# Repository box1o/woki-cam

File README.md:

# woki cam

modular infrared camera for optical tracking of retroreflective markers.

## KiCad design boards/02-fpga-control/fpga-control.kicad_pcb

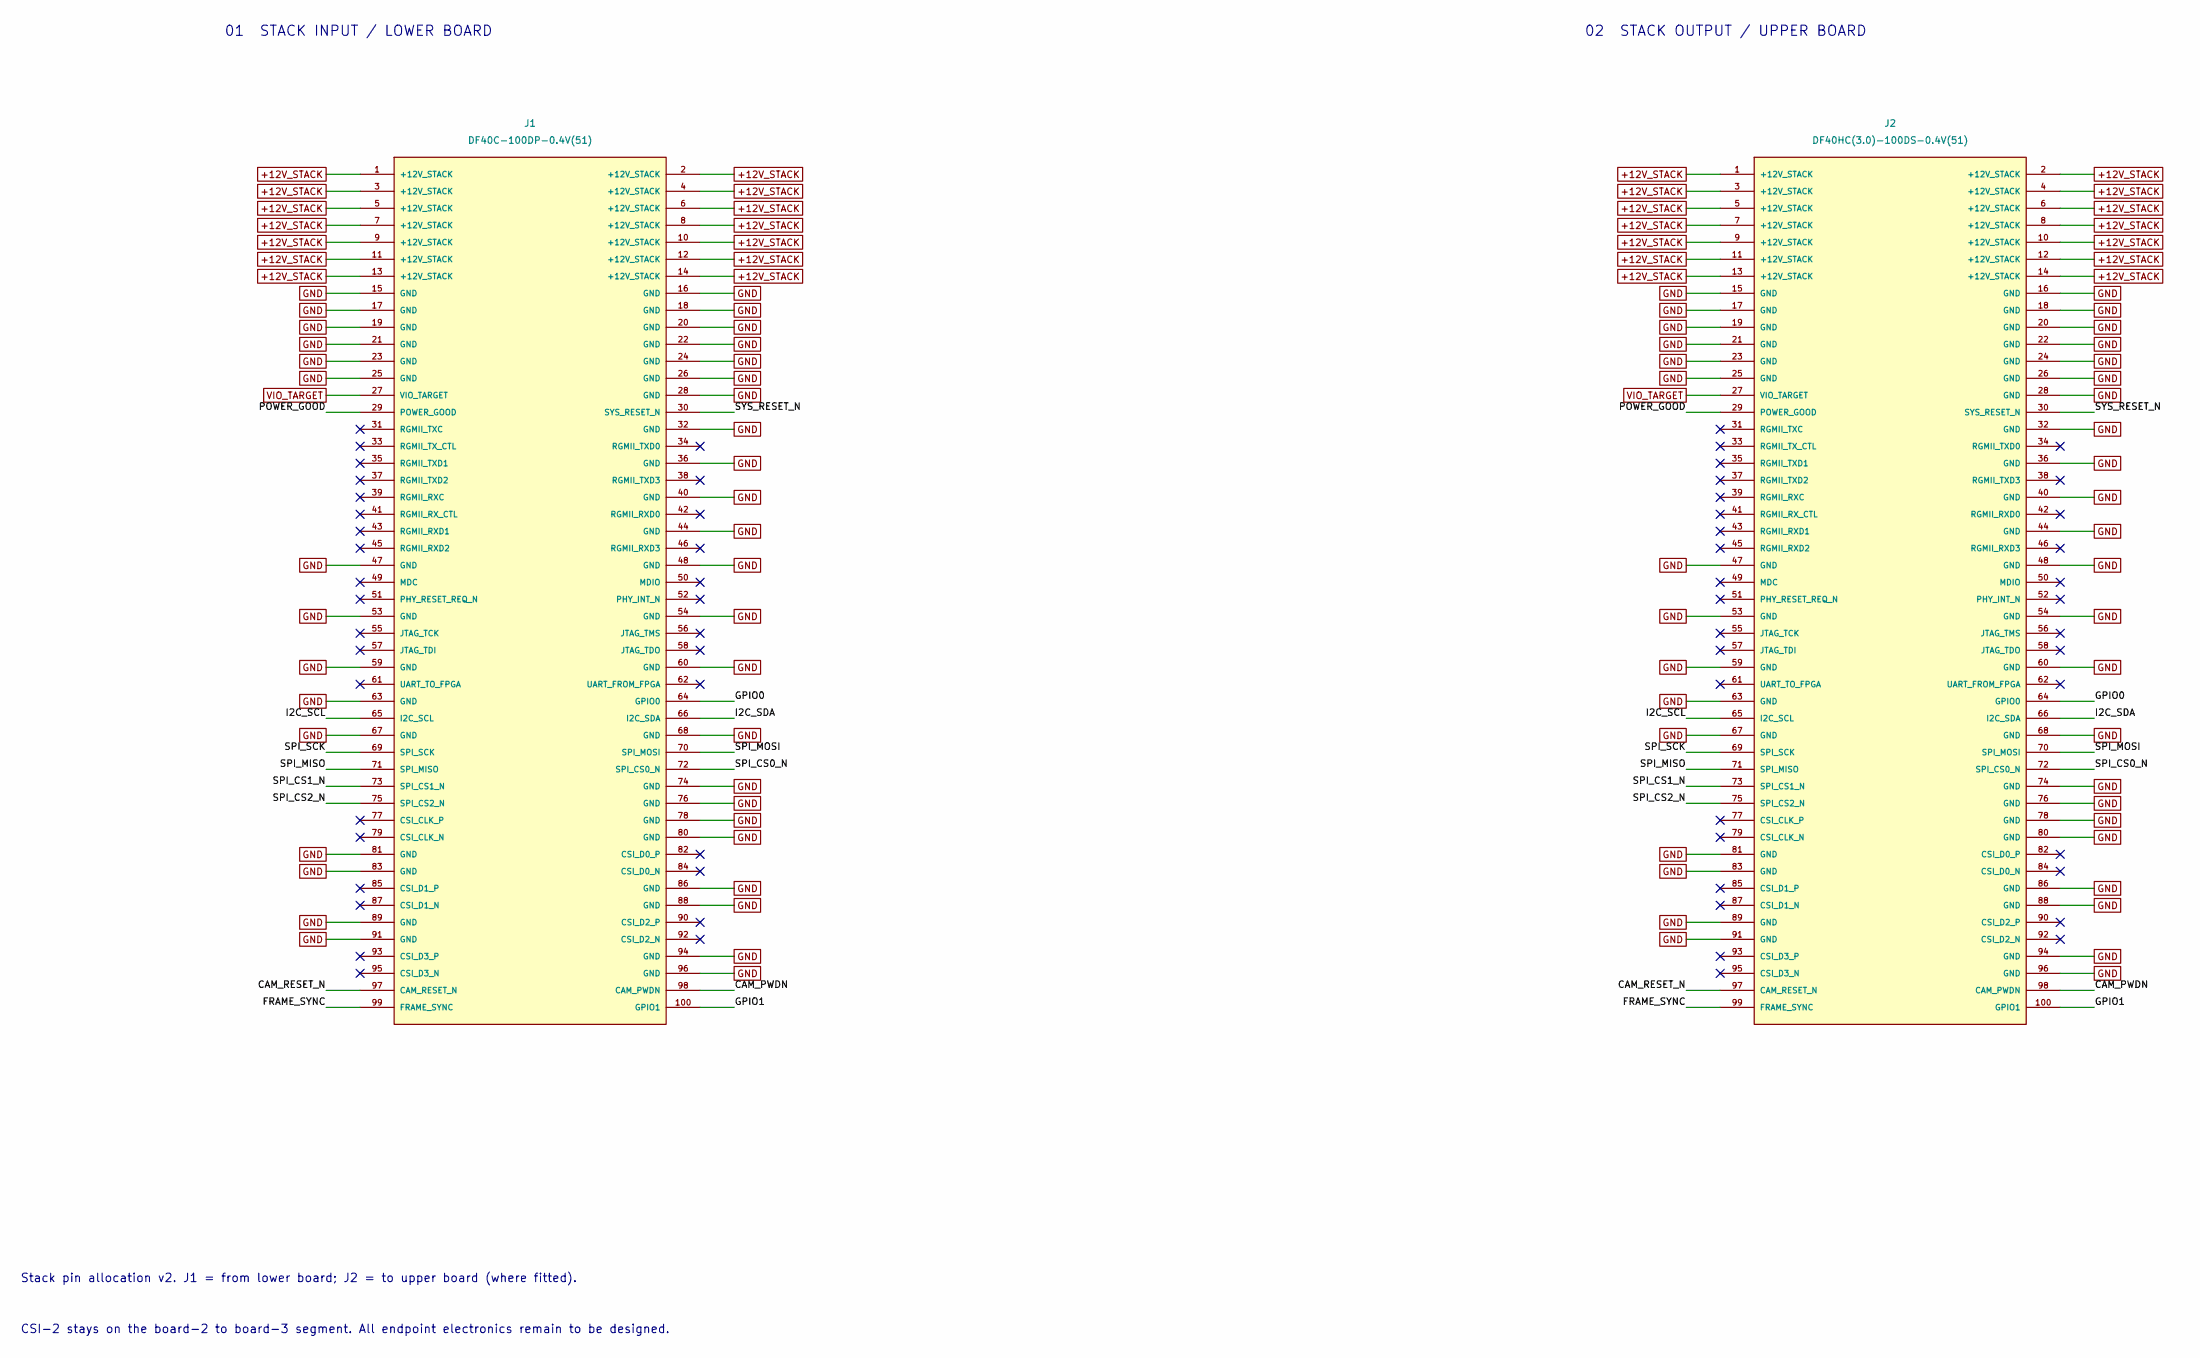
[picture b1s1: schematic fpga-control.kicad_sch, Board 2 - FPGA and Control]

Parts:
J1: DF40C-100DP-0.4V(51); df40c-100dp-0.4v-51
J2: DF40HC(3.0)-100DS-0.4V(51); df40hc-3.0-100ds-0.4v-51

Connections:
+12V_STACK: J1.1 (+12V_STACK), J1.2 (+12V_STACK), J1.3 (+12V_STACK), J1.4 (+12V_STACK), J1.5 (+12V_STACK), J1.6 (+12V_STACK), J1.7 (+12V_STACK), J1.8 (+12V_STACK), J1.9 (+12V_STACK), J1.10 (+12V_STACK), J1.11 (+12V_STACK), J1.12 (+12V_STACK), J1.13 (+12V_STACK), J1.14 (+12V_STACK), J2.1 (+12V_STACK), J2.2 (+12V_STACK), J2.3 (+12V_STACK), J2.4 (+12V_STACK), J2.5 (+12V_STACK), J2.6 (+12V_STACK), J2.7 (+12V_STACK), J2.8 (+12V_STACK), J2.9 (+12V_STACK), J2.10 (+12V_STACK), J2.11 (+12V_STACK), J2.12 (+12V_STACK), J2.13 (+12V_STACK), J2.14 (+12V_STACK)
/CAM_PWDN: J1.98 (CAM_PWDN), J2.98 (CAM_PWDN)
/CAM_RESET_N: J1.97 (CAM_RESET_N), J2.97 (CAM_RESET_N)
/FRAME_SYNC: J1.99 (FRAME_SYNC), J2.99 (FRAME_SYNC)
/GPIO0: J1.64 (GPIO0), J2.64 (GPIO0)
/GPIO1: J1.100 (GPIO1), J2.100 (GPIO1)
/I2C_SCL: J1.65 (I2C_SCL), J2.65 (I2C_SCL)
/I2C_SDA: J1.66 (I2C_SDA), J2.66 (I2C_SDA)
/POWER_GOOD: J1.29 (POWER_GOOD), J2.29 (POWER_GOOD)
/SPI_CS0_N: J1.72 (SPI_CS0_N), J2.72 (SPI_CS0_N)
/SPI_CS1_N: J1.73 (SPI_CS1_N), J2.73 (SPI_CS1_N)
/SPI_CS2_N: J1.75 (SPI_CS2_N), J2.75 (SPI_CS2_N)
/SPI_MISO: J1.71 (SPI_MISO), J2.71 (SPI_MISO)
/SPI_MOSI: J1.70 (SPI_MOSI), J2.70 (SPI_MOSI)
/SPI_SCK: J1.69 (SPI_SCK), J2.69 (SPI_SCK)
/SYS_RESET_N: J1.30 (SYS_RESET_N), J2.30 (SYS_RESET_N)
GND: J1.15 (GND), J1.16 (GND), J1.17 (GND), J1.18 (GND), J1.19 (GND), J1.20 (GND), J1.21 (GND), J1.22 (GND), J1.23 (GND), J1.24 (GND), J1.25 (GND), J1.26 (GND), J1.28 (GND), J1.32 (GND), J1.36 (GND), J1.40 (GND), J1.44 (GND), J1.47 (GND), J1.48 (GND), J1.53 (GND), J1.54 (GND), J1.59 (GND), J1.60 (GND), J1.63 (GND), J1.67 (GND), J1.68 (GND), J1.74 (GND), J1.76 (GND), J1.78 (GND), J1.80 (GND), J1.81 (GND), J1.83 (GND), J1.86 (GND), J1.88 (GND), J1.89 (GND), J1.91 (GND), J1.94 (GND), J1.96 (GND), J2.15 (GND), J2.16 (GND), J2.17 (GND), J2.18 (GND), J2.19 (GND), J2.20 (GND), J2.21 (GND), J2.22 (GND), J2.23 (GND), J2.24 (GND), J2.25 (GND), J2.26 (GND), J2.28 (GND), J2.32 (GND), J2.36 (GND), J2.40 (GND), J2.44 (GND), J2.47 (GND), J2.48 (GND), J2.53 (GND), J2.54 (GND), J2.59 (GND), J2.60 (GND), J2.63 (GND), J2.67 (GND), J2.68 (GND), J2.74 (GND), J2.76 (GND), J2.78 (GND), J2.80 (GND), J2.81 (GND), J2.83 (GND), J2.86 (GND), J2.88 (GND), J2.89 (GND), J2.91 (GND), J2.94 (GND), J2.96 (GND)
VIO_TARGET: J1.27 (VIO_TARGET), J2.27 (VIO_TARGET)

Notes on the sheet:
Stack pin allocation v2. J1 = from lower board; J2 = to upper board (where fitted).
CSI-2 stays on the board-2 to board-3 segment. All endpoint electronics remain to be designed.
01 STACK INPUT / LOWER BOARD
02 STACK OUTPUT / UPPER BOARD

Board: 8 copper layers, 6 parts (1 on the bottom side), 18 nets, no tracks yet.

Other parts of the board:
H1, H2, H3, H4: MNT_HOLE_M3; mounting-hole-m3

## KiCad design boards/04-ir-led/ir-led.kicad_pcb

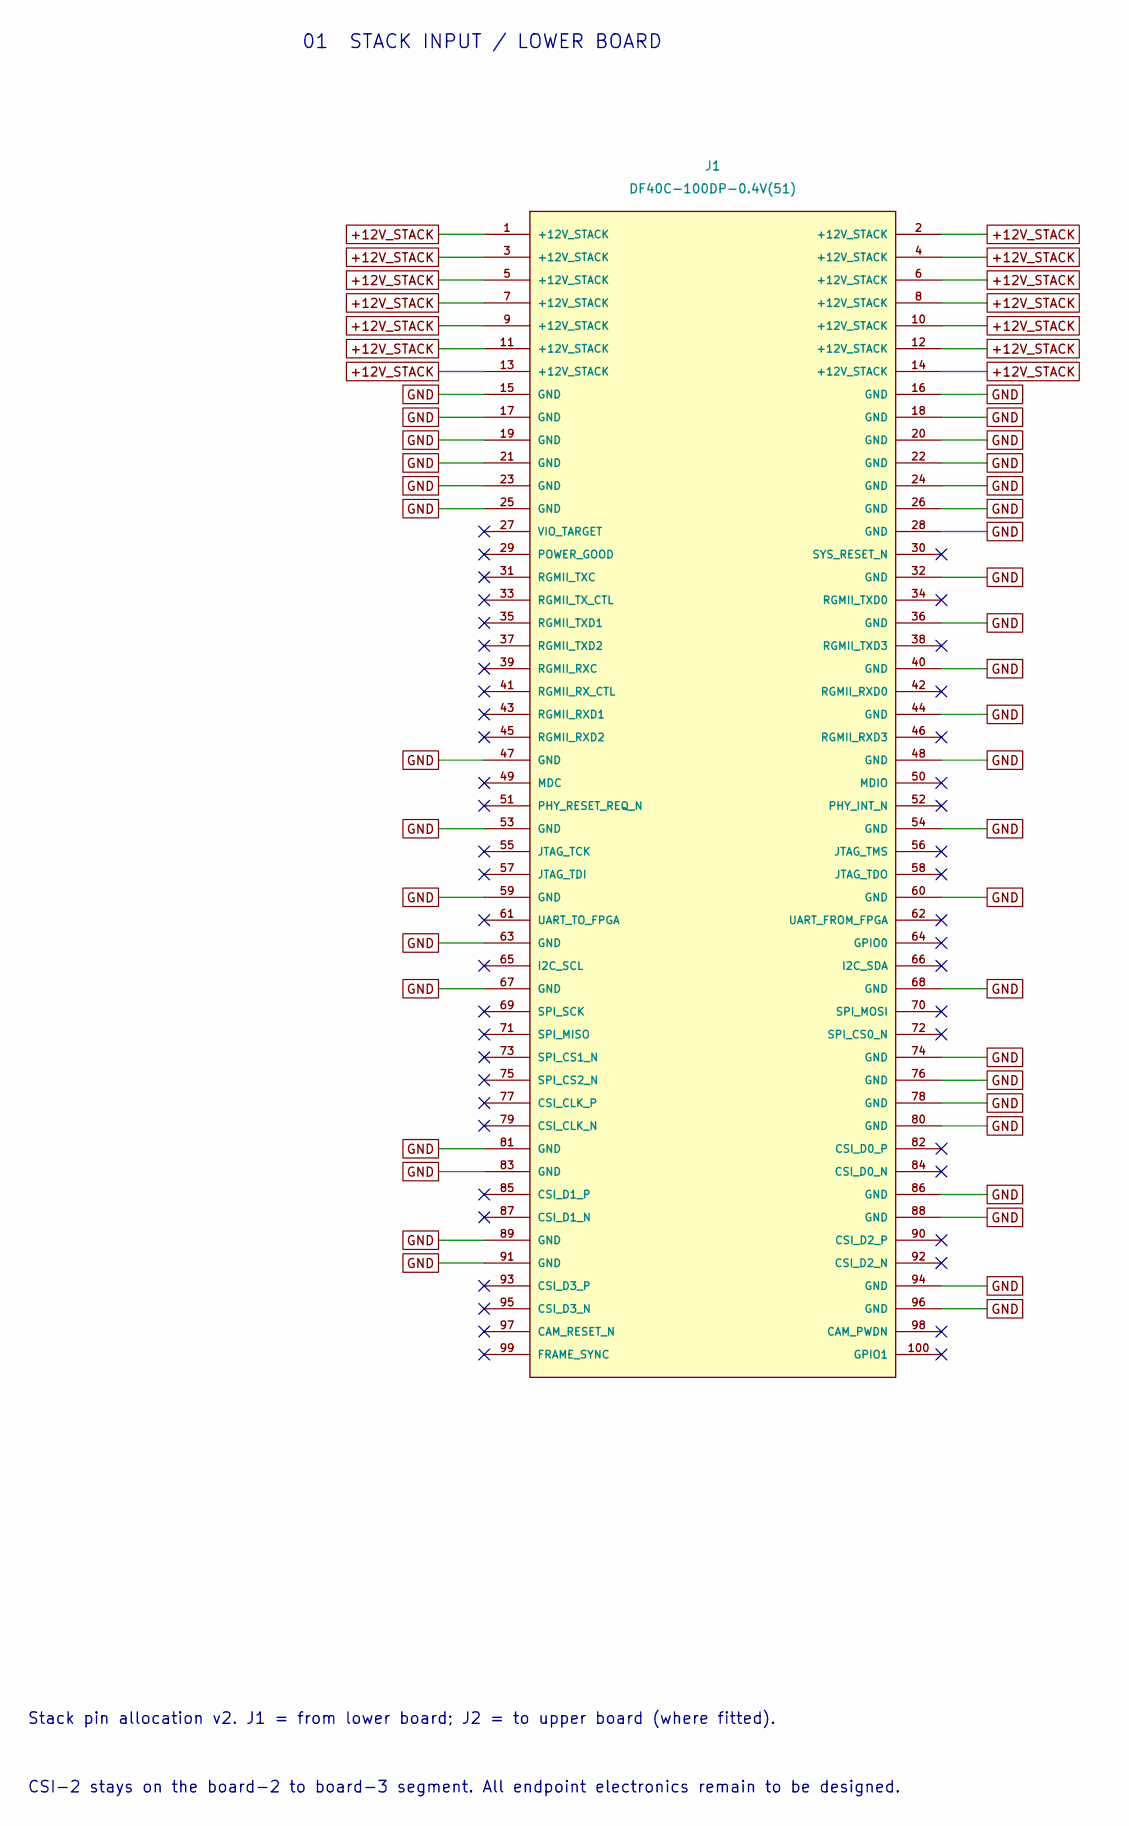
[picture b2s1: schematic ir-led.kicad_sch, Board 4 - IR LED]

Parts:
J1: DF40C-100DP-0.4V(51); df40c-100dp-0.4v-51

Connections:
+12V_STACK: J1.1 (+12V_STACK), J1.2 (+12V_STACK), J1.3 (+12V_STACK), J1.4 (+12V_STACK), J1.5 (+12V_STACK), J1.6 (+12V_STACK), J1.7 (+12V_STACK), J1.8 (+12V_STACK), J1.9 (+12V_STACK), J1.10 (+12V_STACK), J1.11 (+12V_STACK), J1.12 (+12V_STACK), J1.13 (+12V_STACK), J1.14 (+12V_STACK)
GND: J1.15 (GND), J1.16 (GND), J1.17 (GND), J1.18 (GND), J1.19 (GND), J1.20 (GND), J1.21 (GND), J1.22 (GND), J1.23 (GND), J1.24 (GND), J1.25 (GND), J1.26 (GND), J1.28 (GND), J1.32 (GND), J1.36 (GND), J1.40 (GND), J1.44 (GND), J1.47 (GND), J1.48 (GND), J1.53 (GND), J1.54 (GND), J1.59 (GND), J1.60 (GND), J1.63 (GND), J1.67 (GND), J1.68 (GND), J1.74 (GND), J1.76 (GND), J1.78 (GND), J1.80 (GND), J1.81 (GND), J1.83 (GND), J1.86 (GND), J1.88 (GND), J1.89 (GND), J1.91 (GND), J1.94 (GND), J1.96 (GND)

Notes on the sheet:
Stack pin allocation v2. J1 = from lower board; J2 = to upper board (where fitted).
CSI-2 stays on the board-2 to board-3 segment. All endpoint electronics remain to be designed.
01 STACK INPUT / LOWER BOARD

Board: 8 copper layers, 5 parts (1 on the bottom side), 2 nets, no tracks yet.

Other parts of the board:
H1, H2, H3, H4: MNT_HOLE_M3; mounting-hole-m3

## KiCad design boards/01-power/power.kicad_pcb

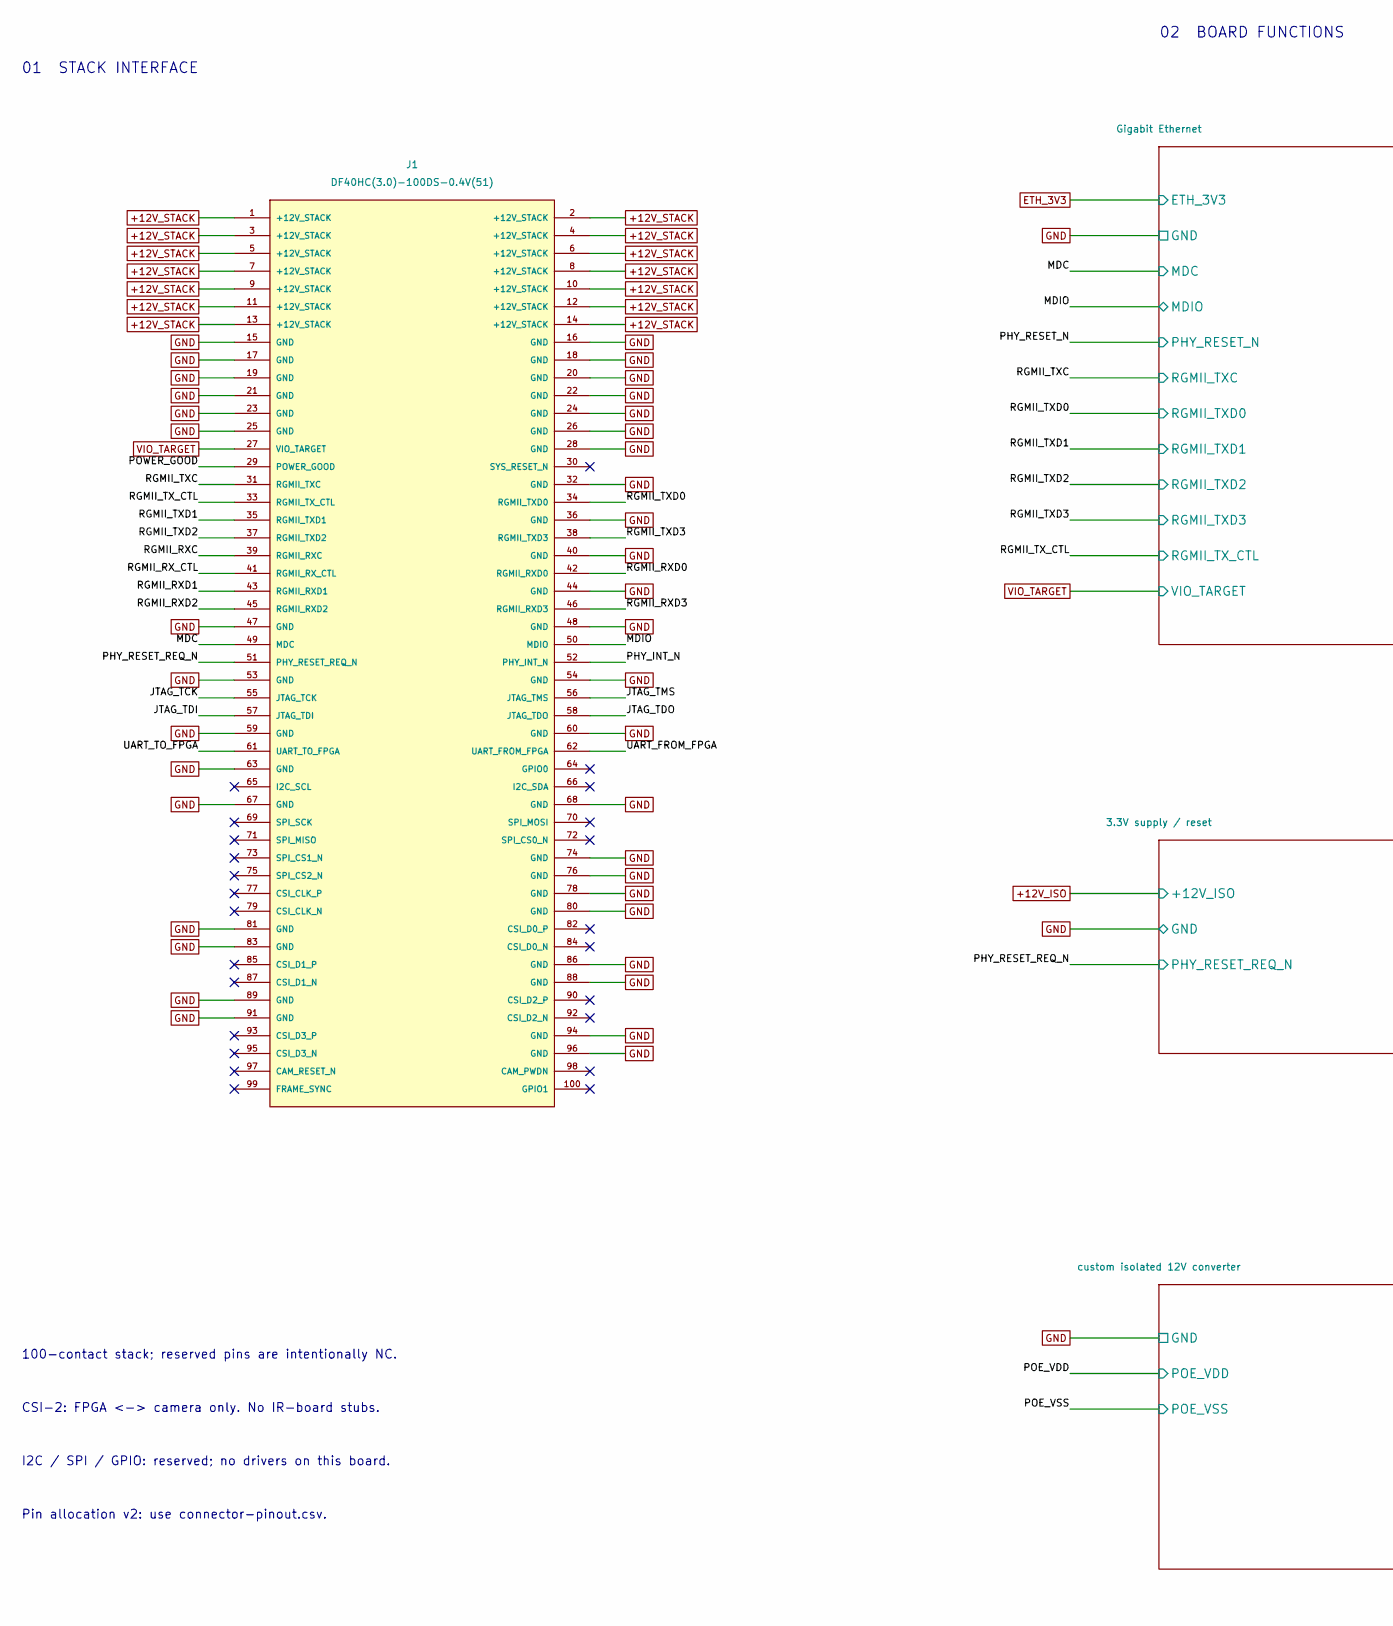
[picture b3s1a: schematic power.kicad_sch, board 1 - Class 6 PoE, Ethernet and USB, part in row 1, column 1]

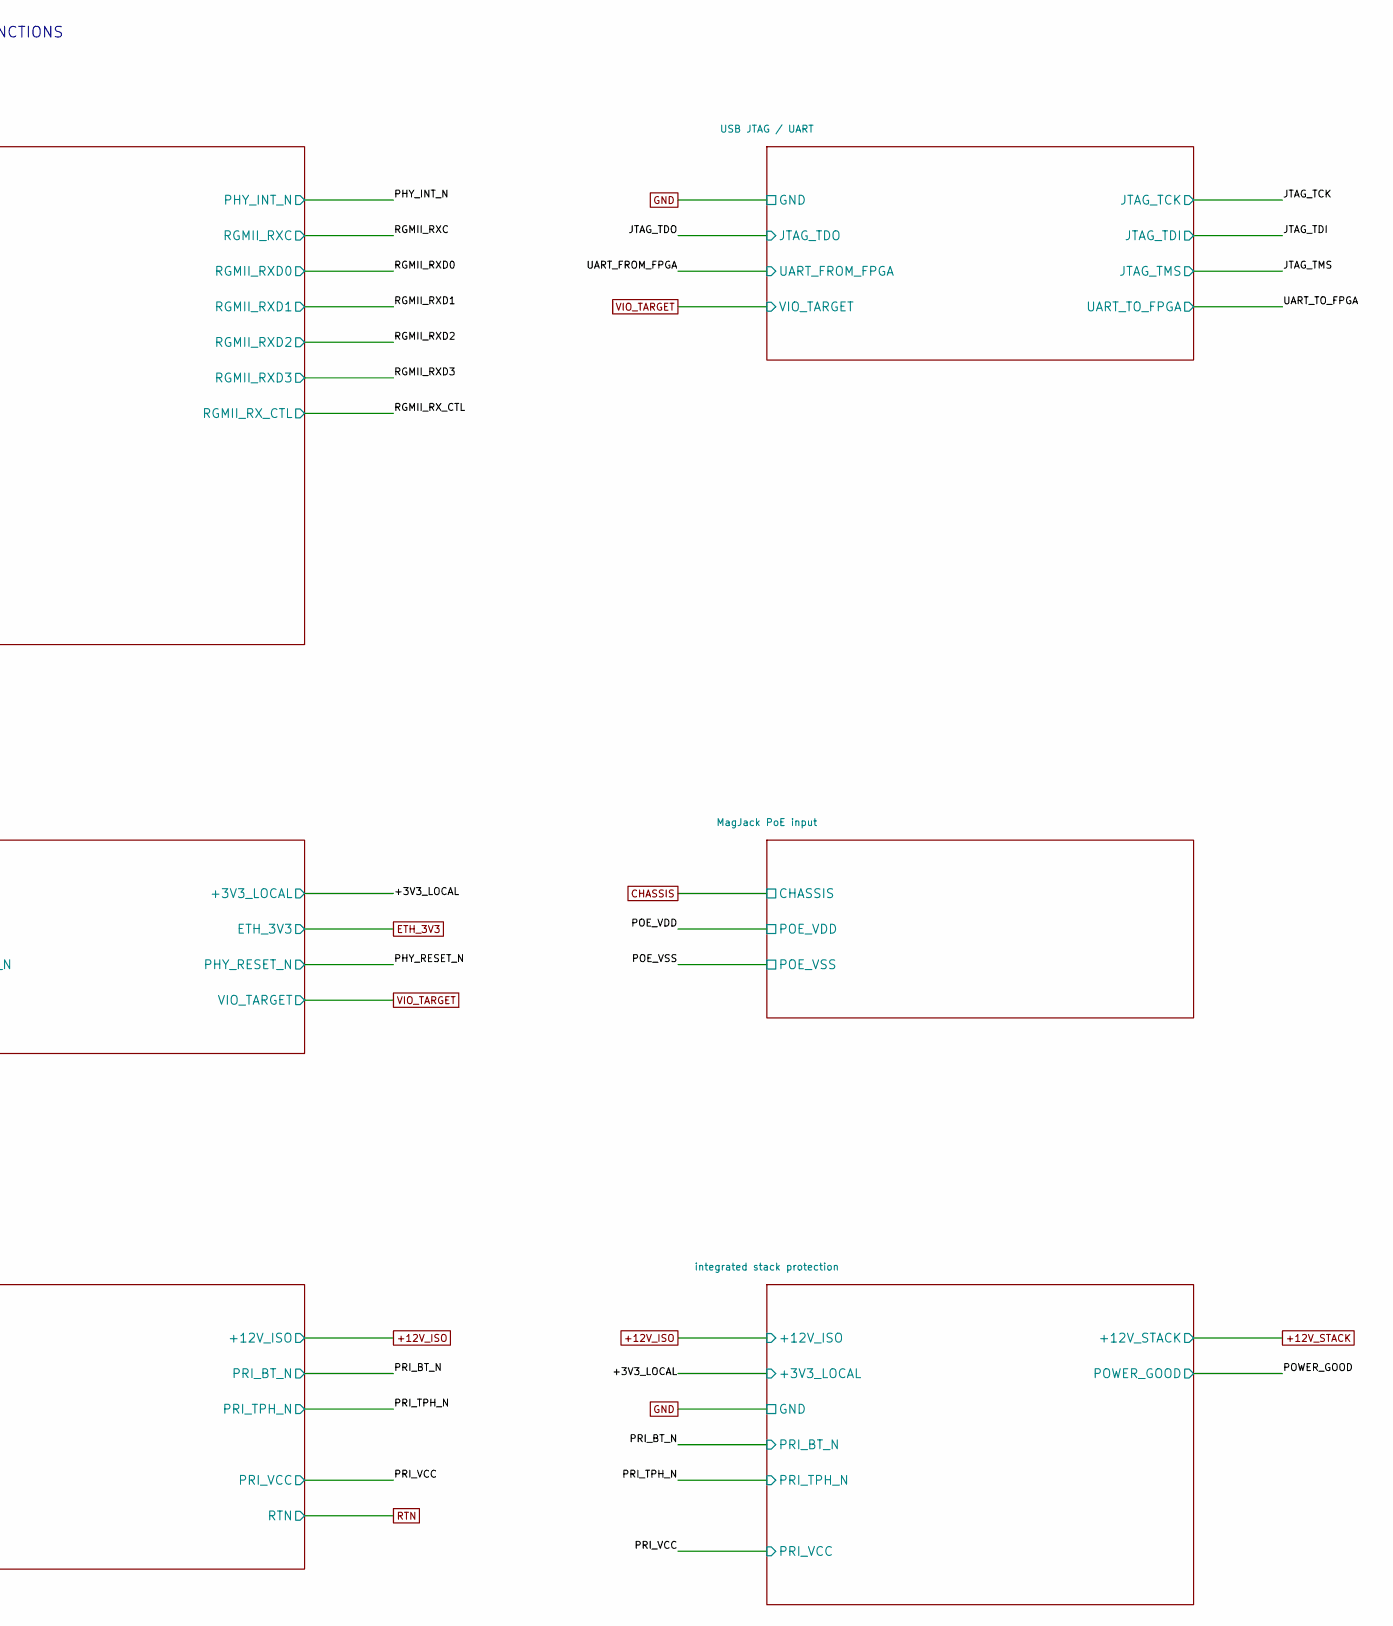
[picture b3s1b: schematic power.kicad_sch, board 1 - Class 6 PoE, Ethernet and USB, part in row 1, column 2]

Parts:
J1: DF40HC(3.0)-100DS-0.4V(51); df40hc-3.0-100ds-0.4v-51

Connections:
+12V_STACK: J1.1 (+12V_STACK), J1.2 (+12V_STACK), J1.3 (+12V_STACK), J1.4 (+12V_STACK), J1.5 (+12V_STACK), J1.6 (+12V_STACK), J1.7 (+12V_STACK), J1.8 (+12V_STACK), J1.9 (+12V_STACK), J1.10 (+12V_STACK), J1.11 (+12V_STACK), J1.12 (+12V_STACK), J1.13 (+12V_STACK), J1.14 (+12V_STACK); also elsewhere on the board
/JTAG_TCK: J1.55 (JTAG_TCK); also elsewhere on the board
/JTAG_TDI: J1.57 (JTAG_TDI); also elsewhere on the board
/JTAG_TDO: J1.58 (JTAG_TDO); also elsewhere on the board
/JTAG_TMS: J1.56 (JTAG_TMS); also elsewhere on the board
/MDC: J1.49 (MDC); also elsewhere on the board
/MDIO: J1.50 (MDIO); also elsewhere on the board
/PHY_INT_N: J1.52 (PHY_INT_N); also elsewhere on the board
/PHY_RESET_REQ_N: J1.51 (PHY_RESET_REQ_N); also elsewhere on the board
/POWER_GOOD: J1.29 (POWER_GOOD); also elsewhere on the board
/RGMII_RXC: J1.39 (RGMII_RXC); also elsewhere on the board
/RGMII_RXD0: J1.42 (RGMII_RXD0); also elsewhere on the board
/RGMII_RXD1: J1.43 (RGMII_RXD1); also elsewhere on the board
/RGMII_RXD2: J1.45 (RGMII_RXD2); also elsewhere on the board
/RGMII_RXD3: J1.46 (RGMII_RXD3); also elsewhere on the board
/RGMII_RX_CTL: J1.41 (RGMII_RX_CTL); also elsewhere on the board
/RGMII_TXC: J1.31 (RGMII_TXC); also elsewhere on the board
/RGMII_TXD0: J1.34 (RGMII_TXD0); also elsewhere on the board
/RGMII_TXD1: J1.35 (RGMII_TXD1); also elsewhere on the board
/RGMII_TXD2: J1.37 (RGMII_TXD2); also elsewhere on the board
/RGMII_TXD3: J1.38 (RGMII_TXD3); also elsewhere on the board
/RGMII_TX_CTL: J1.33 (RGMII_TX_CTL); also elsewhere on the board
/UART_FROM_FPGA: J1.62 (UART_FROM_FPGA); also elsewhere on the board
/UART_TO_FPGA: J1.61 (UART_TO_FPGA); also elsewhere on the board
VIO_TARGET: J1.27 (VIO_TARGET); also elsewhere on the board

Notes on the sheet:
CSI-2: FPGA <-> camera only. No IR-board stubs.
Pin allocation v2: use connector-pinout.csv.
I2C / SPI / GPIO: reserved; no drivers on this board.
100-contact stack; reserved pins are intentionally NC.
01 STACK INTERFACE
02 BOARD FUNCTIONS

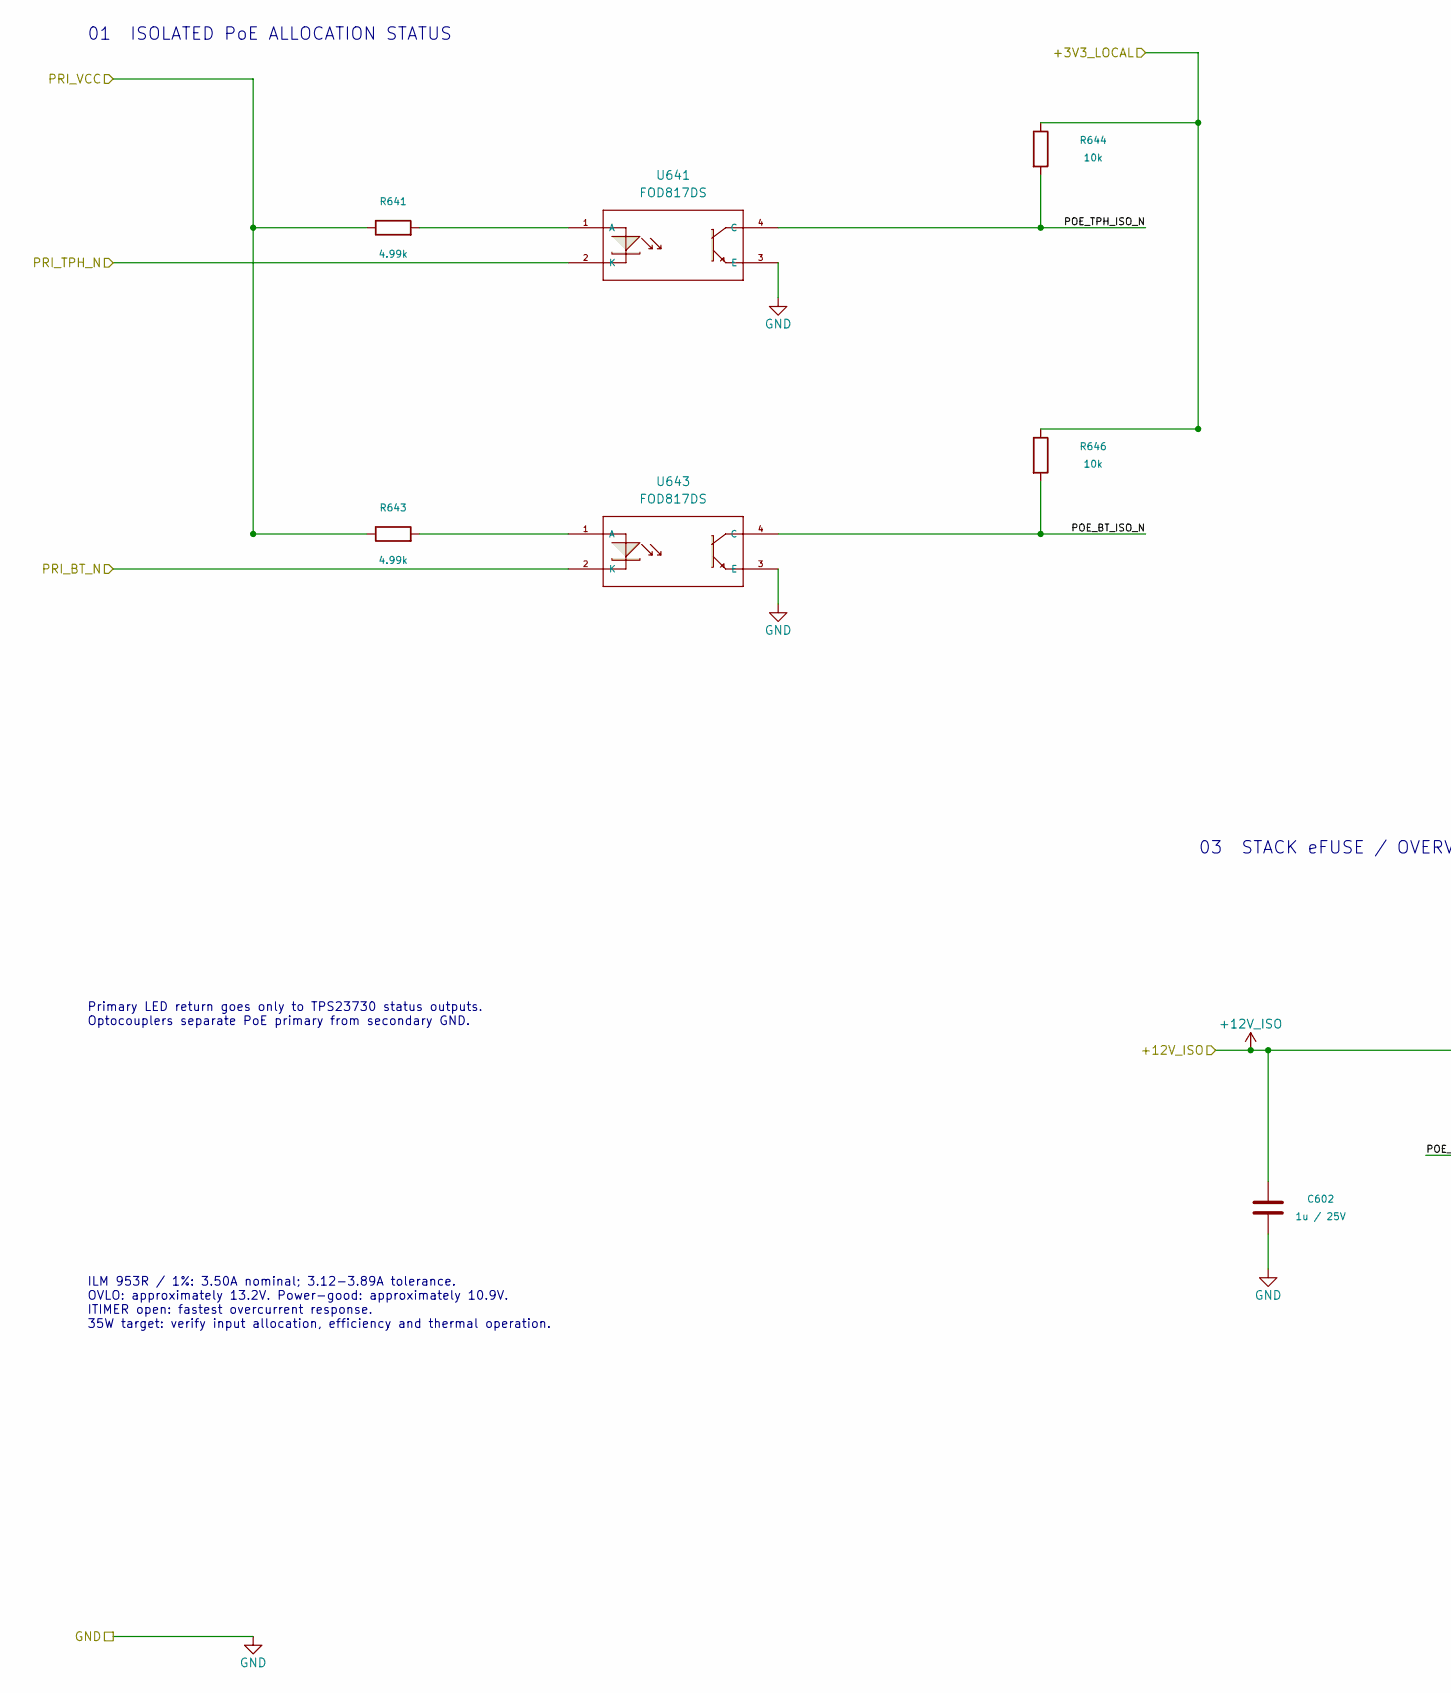
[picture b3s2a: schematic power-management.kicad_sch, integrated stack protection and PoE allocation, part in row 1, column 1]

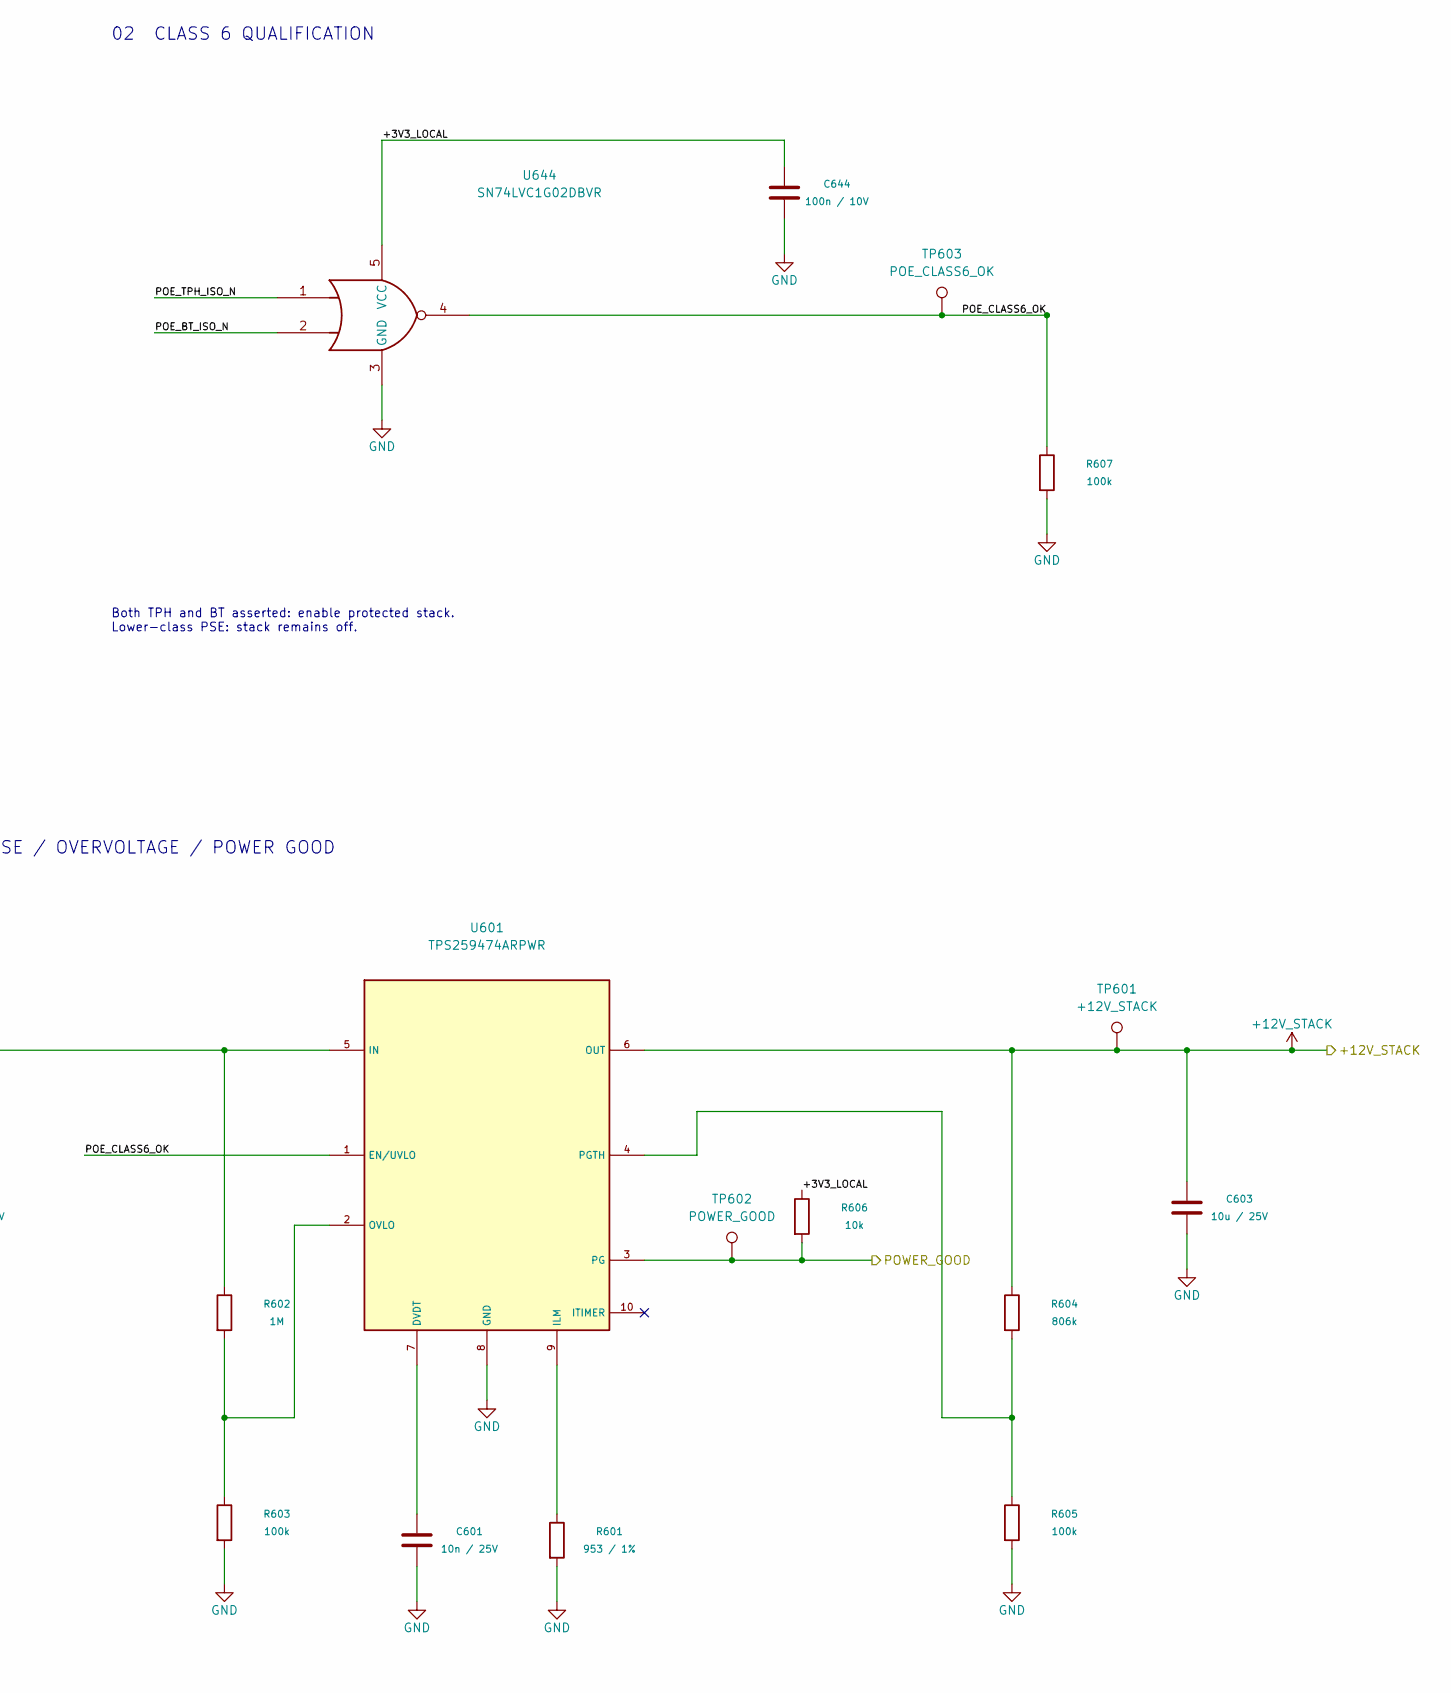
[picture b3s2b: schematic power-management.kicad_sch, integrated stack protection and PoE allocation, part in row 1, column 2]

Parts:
C601: 10n / 25V; C_0805_2012Metric
C602: 1u / 25V; C_0805_2012Metric
C603: 10u / 25V; C_0805_2012Metric
C644: 100n / 10V; C_0603_1608Metric
R601: 953 / 1%; R_0603_1608Metric
R602: 1M; R_0603_1608Metric
R603, R605, R607: 100k; R_0603_1608Metric
R604: 806k; R_0603_1608Metric
R606, R644, R646: 10k; R_0603_1608Metric
R641, R643: 4.99k; R_0603_1608Metric
TP601: +12V_STACK; TestPoint_Pad_D1.5mm
TP602: POWER_GOOD; TestPoint_Pad_D1.5mm
TP603: POE_CLASS6_OK; TestPoint_Pad_D1.5mm
U601: TPS259474ARPWR; tps259474arpwr
U641, U643: FOD817DS; fod817ds
U644: SN74LVC1G02DBVR; SOT-23-5

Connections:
+12V_ISO: C602.1, R602.1, U601.5 (IN); also elsewhere on the board
+12V_STACK: C603.1, R604.1, TP601.1 (1_1), U601.6 (OUT); also elsewhere on the board
/+3V3_LOCAL: C644.1, R606.1, R644.1, R646.1, U644.5 (VCC); also elsewhere on the board
/POWER_GOOD: R606.2, TP602.1 (1_1), U601.3 (PG); also elsewhere on the board
/PRI_BT_N: U643.2 (K); also elsewhere on the board
/PRI_TPH_N: U641.2 (K); also elsewhere on the board
/PRI_VCC: R641.1, R643.1; also elsewhere on the board
/integrated stack protection/POE_BT_ISO_N: R646.2, U643.4 (C), U644.2
/integrated stack protection/POE_CLASS6_OK: R607.1, TP603.1 (1_1), U601.1 (EN/UVLO), U644.4
/integrated stack protection/POE_TPH_ISO_N: R644.2, U641.4 (C), U644.1
unnamed: C601.1, U601.7 (DVDT)
unnamed: R601.1, U601.9 (ILM)
unnamed: R602.2, R603.1, U601.2 (OVLO)
unnamed: R604.2, R605.1, U601.4 (PGTH)
unnamed: R641.2, U641.1 (A)
unnamed: R643.2, U643.1 (A)

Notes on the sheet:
03 STACK eFUSE / OVERVOLTAGE / POWER GOOD
02 CLASS 6 QUALIFICATION
ILM 953R / 1%: 3.50A nominal; 3.12-3.89A tolerance. OVLO: approximately 13.2V. Power-good: approximately 10.9V. ITIMER open: fastest overcurrent response. 35W target: verify input allocation, efficiency and thermal operation.
Both TPH and BT asserted: enable protected stack. Lower-class PSE: stack remains off.
01 ISOLATED PoE ALLOCATION STATUS
Primary LED return goes only to TPS23730 status outputs. Optocouplers separate PoE primary from secondary GND.
